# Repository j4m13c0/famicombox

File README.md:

The FamicomBox+ mod has been designed to fix some of the design limitations in the Famicom Box design. The Famicom Box is designed to switch between 16 different cartridges, however in the original design some of the pins in the cartridge are common between the 16 cartridges such as IRQ, M2 and PPU /RD. This mod addresses the following issues:

* Demultiplexes M2 (Pin 38) to all 16 Cartridges
* Multiplexes /IRQ (Pin 15) from all 16 cartridges
* Multiplexes CIRAM /CE (Pin 57) from all 16 cartirdges
* Demultiplexes PPU A12 (pin 64) to all 16 Cartridges
* Demultiplexes PPU /RD (Pin 21) to all 16 Cartridges
* Supplies PPU /A13 (Pin 58) to all cartridges
* Isolates EXP0, EXP1, EXP2, EXP3, EXP4, EXP5, EXP7, EXP8 and EXP9 
* Allows 2 cartridges to utilise EXP6 for Expansion Audio with volume control. 
* Fixes an issue with open bus on games such as Paper Boy
* Disables the second RAM chip 6000 - 7FFF when in game, to allow SRAM and other functions. 
* Enables / Disables $5xxx when in game, this is used in some games and the Everdrive. 

### Famicom Box Warning

On a stock Famicom Box, the EXP Lines are connected to 5V or GND depending on which slot you use. This is used with the CIC to address each CIC individually. Some cartridges use these ports for debugging, Audio etc. If you have a stock Famicom Box you will damage certain cartridge if you plug them in.

### Limitations
This mod is rather complicated to install as there are many parts that you will need to modify to get it to work. You will need to have prior experience with de-soldering IC chips, soldering mod wires and debugging any issues that arise. 
This mod will not work with modern games that have tighter timings, as well as bootleg games bought from places such as AliExpress. 

### Tested Games
I have tested this with the following games:

* Castlevania 3 (Famicom with Expansion Audio)
* The Legend of Zelda
* The Adventure of Link
* Super Mario Bros
* Super Mario Bros 2
* Super Mario Bros 3
* Gauntlet II
* Tetris
* Snake Rattle N Roll
* The Little Mermaid
* Excitebike
* Tennis
* Duck Hunt
* Wrecking Crew
* Captain Planet and the Planeteers
* High Speed
* Yoshi 

I have also been able to use the Famicom Disk System, the RAM adapter will fit in Slot 14. The mod also works with an Everdrive. 

__There may be some games that will not work on this system. This could be down to timing issues. I cannot guarantee any game will work outside of the games tested.__

### Menu System 
The Menu system has been designed by Nintendo to check an internal database of games or for the Nintendo Header in the ROM. Most games do not have a correct header and will not be in the database, thus the game will be rejected. 
 
To get around this, we have modified the menu to still allow games to show up in the menu, however it will only display "NES GAME" instead of the actual game name. 

### 3D Prints
I have included some 3D prints that have used with the Famicom Box.  
 
The Modulator 3D print I used to replace the modulator with some custom connectors with my Famicom Box, I had fitted an NESRGB and this was where I mounted the video and audio connections. This is not required, but added incase you also want to RGB yours. 

The Replacement Coin box covers are the 2 covers on the right-hand side. If you remove the coinbox, you will need these to cover up the holes. 

The 72 Pin connector spacer is helpful if you use the Aliexpress connectors. See the installation guide for more details. 

### Special Thanks

I would like to thank Lidnariq for his time and knowledge to help me make this idea a reality, he was there to teach me what parts were different between the Famicom Box and what parts to include on my mod board. 

I would also like to extend a thank you to Fiskbit, who has helped with reverse engineering the Menu software and modifying it to allow other games to function. He has also improved the menu and fixed some bugs. 
The boot up of the console is now drastically improved due to changes made to the menu.

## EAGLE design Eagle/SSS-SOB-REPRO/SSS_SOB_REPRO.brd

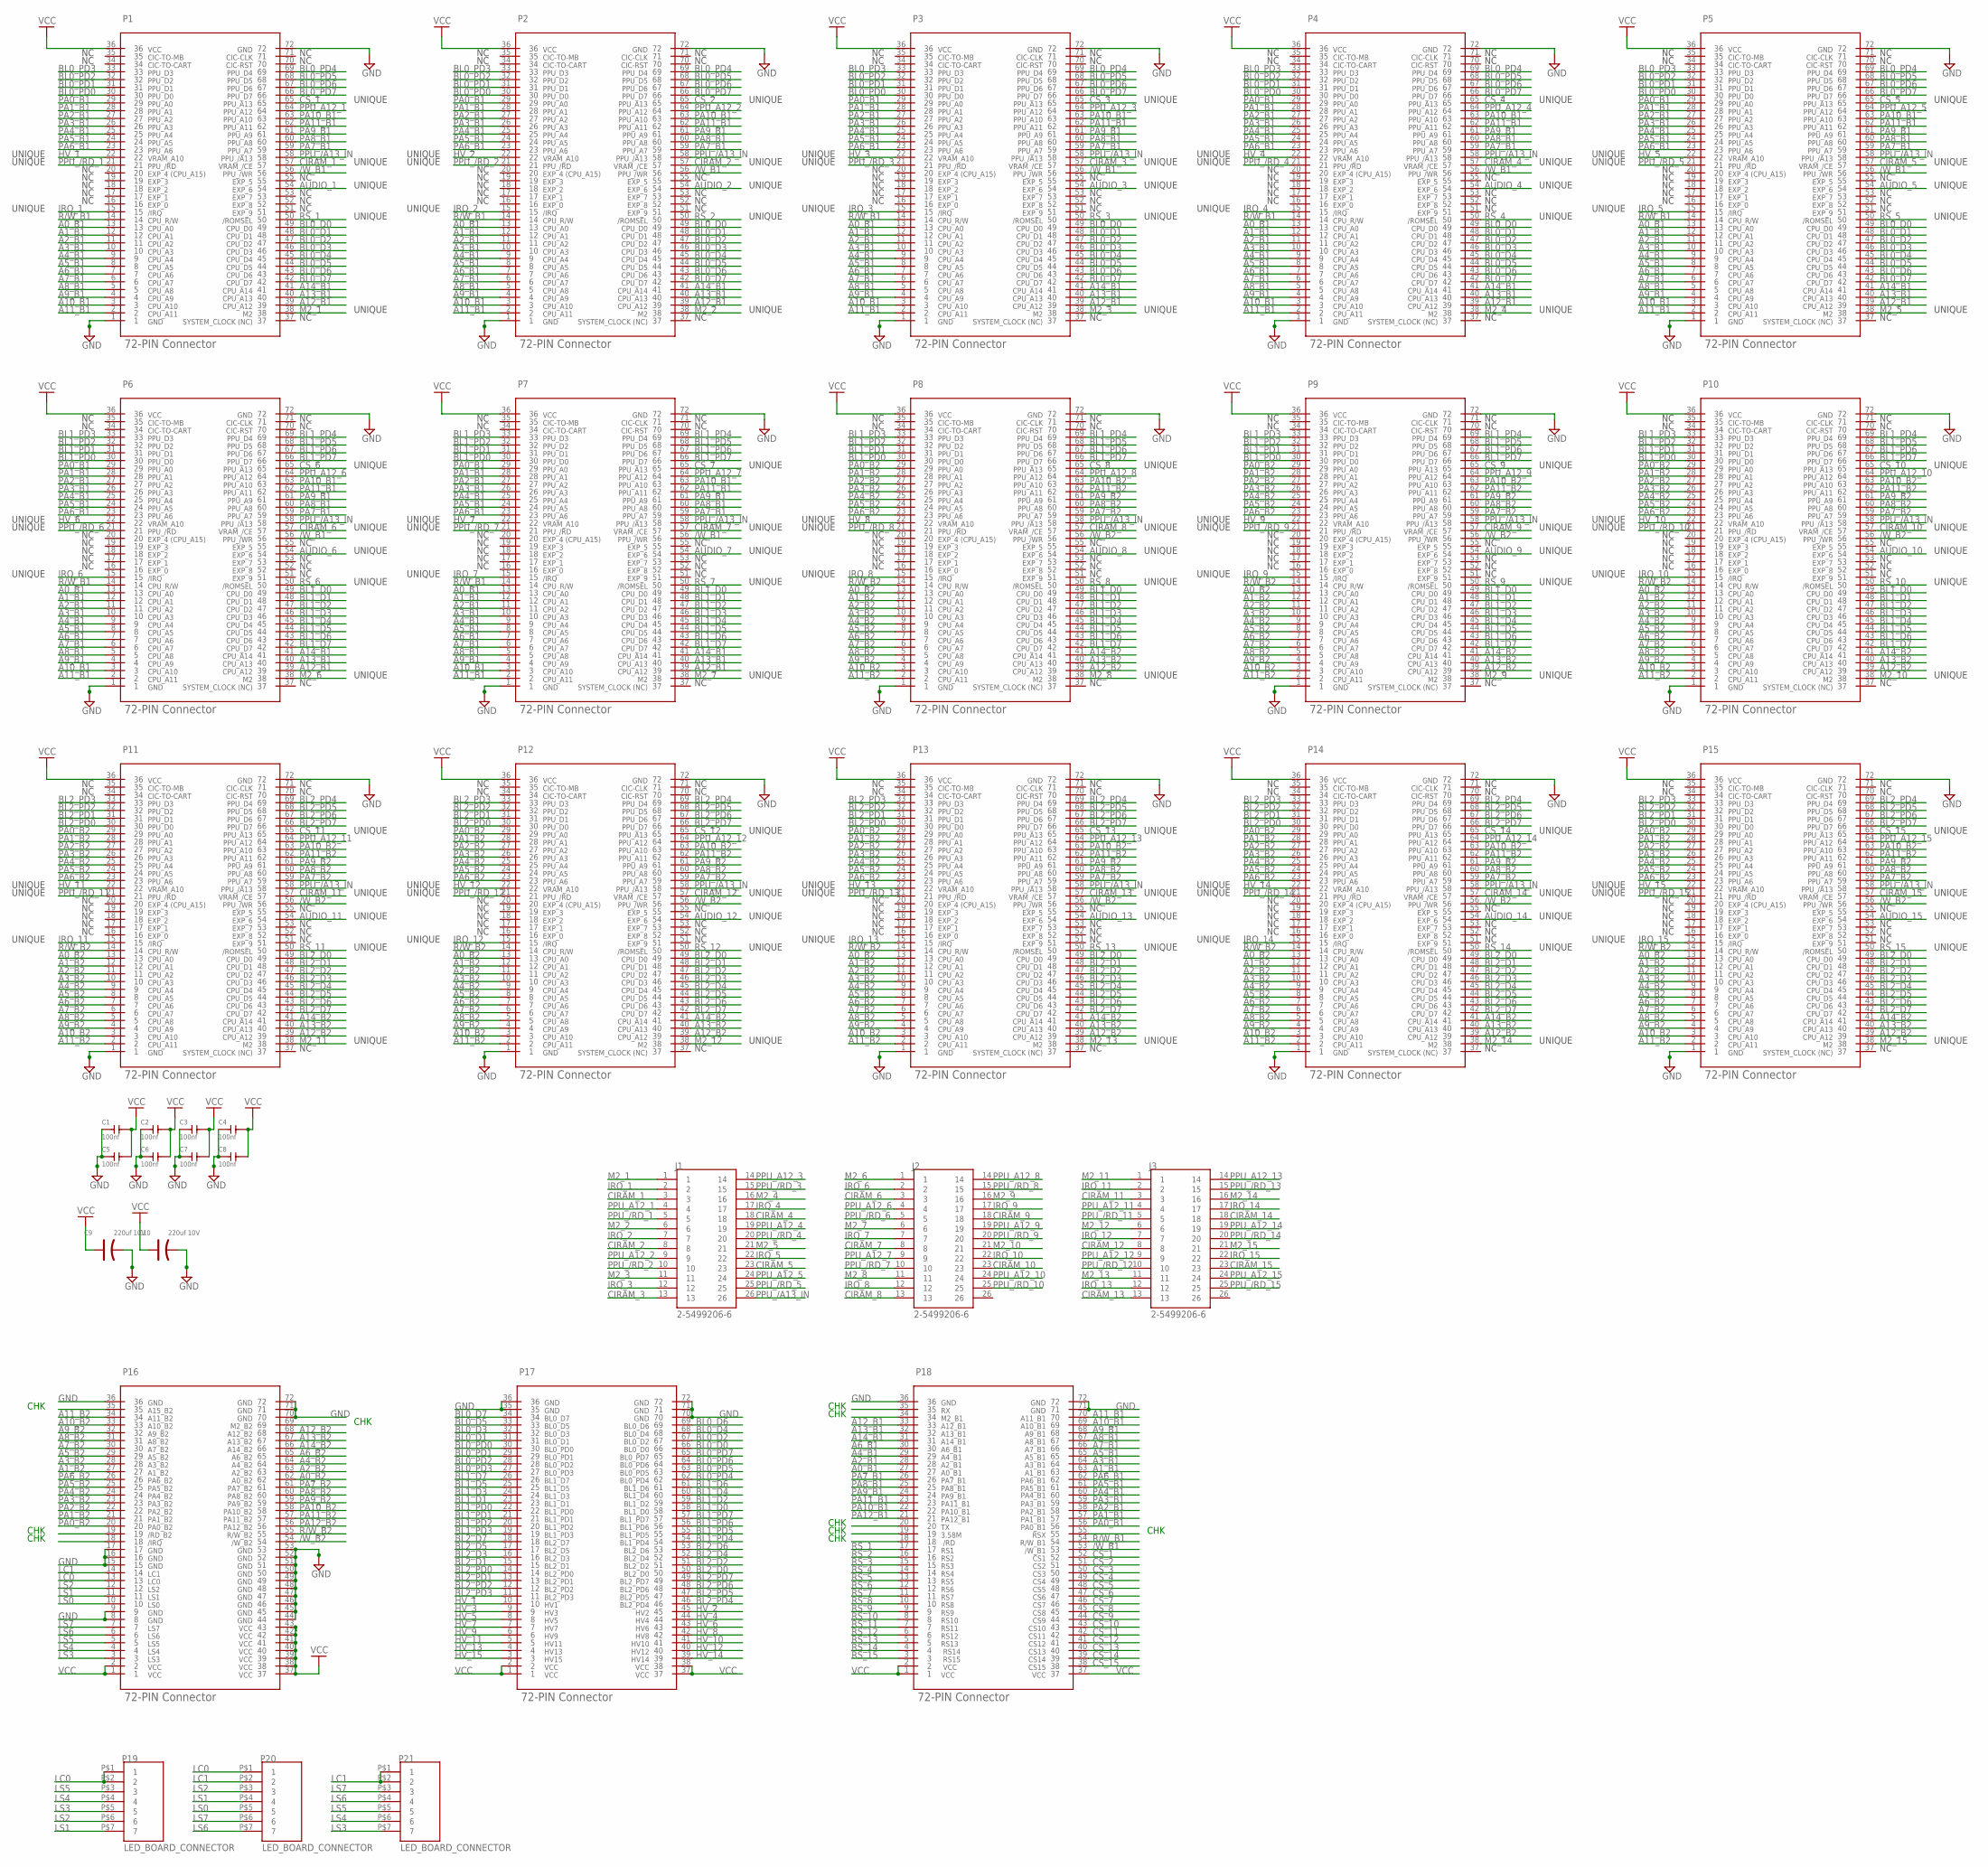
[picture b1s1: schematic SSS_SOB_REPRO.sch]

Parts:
C1, C2, C3, C4, C5, C6, C7, C8: 100nf; C0603
C9, C10: 220uf 10V; PC-D5.3MM
J1, J2, J3: 2-5499206-6; TE_2-5499206-6
P1, P2, P3, P4, P5, P6, P7, P8, P9, P10, P11, P12, P13, P14, P15: CARTRIDGE_CONNECTOR; 72PIN
P16: P16_CONNECTOR; 72PIN
P17: P17_CONNECTOR; 72PIN
P18: P18_CONNECTOR; 72PIN
P19, P20, P21: LED_BOARD_CONNECTOR; 7PIN_LED

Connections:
/RD_B2: P16.19
/W_B1: P1.56, P2.56, P3.56, P4.56, P5.56, P6.56, P7.56, P18.53
/W_B2: P8.56, P9.56, P10.56, P11.56, P12.56, P13.56, P14.56, P15.56, P16.54
A0_B1: P1.13, P2.13, P3.13, P4.13, P5.13, P6.13, P7.13, P18.27
A0_B2: P8.13, P9.13, P10.13, P11.13, P12.13, P13.13, P14.13, P15.13, P16.62
A1_B1: P1.12, P2.12, P3.12, P4.12, P5.12, P6.12, P7.12, P18.63
A1_B2: P8.12, P9.12, P10.12, P11.12, P12.12, P13.12, P14.12, P15.12, P16.27
A2_B1: P1.11, P2.11, P3.11, P4.11, P5.11, P6.11, P7.11, P18.28
A2_B2: P8.11, P9.11, P10.11, P11.11, P12.11, P13.11, P14.11, P15.11, P16.63
A3_B1: P1.10, P2.10, P3.10, P4.10, P5.10, P6.10, P7.10, P18.64
A3_B2: P8.10, P9.10, P10.10, P11.10, P12.10, P13.10, P14.10, P15.10, P16.28
A4_B1: P1.9, P2.9, P3.9, P4.9, P5.9, P6.9, P7.9, P18.29
A4_B2: P8.9, P9.9, P10.9, P11.9, P12.9, P13.9, P14.9, P15.9, P16.64
A5_B1: P1.8, P2.8, P3.8, P4.8, P5.8, P6.8, P7.8, P18.65
A5_B2: P8.8, P9.8, P10.8, P11.8, P12.8, P13.8, P14.8, P15.8, P16.29
A6_B1: P1.7, P2.7, P3.7, P4.7, P5.7, P6.7, P7.7, P18.30
A6_B2: P8.7, P9.7, P10.7, P11.7, P12.7, P13.7, P14.7, P15.7, P16.65
A7_B1: P1.6, P2.6, P3.6, P4.6, P5.6, P6.6, P7.6, P18.66
A7_B2: P8.6, P9.6, P10.6, P11.6, P12.6, P13.6, P14.6, P15.6, P16.30
A8_B1: P1.5, P2.5, P3.5, P4.5, P5.5, P6.5, P7.5, P18.67
A8_B2: P8.5, P9.5, P10.5, P11.5, P12.5, P13.5, P14.5, P15.5, P16.31
A9_B1: P1.4, P2.4, P3.4, P4.4, P5.4, P6.4, P7.4, P18.68
A9_B2: P8.4, P9.4, P10.4, P11.4, P12.4, P13.4, P14.4, P15.4, P16.32
A10_B1: P1.3, P2.3, P3.3, P4.3, P5.3, P6.3, P7.3, P18.69
A10_B2: P8.3, P9.3, P10.3, P11.3, P12.3, P13.3, P14.3, P15.3, P16.33
A11_B1: P1.2, P2.2, P3.2, P4.2, P5.2, P6.2, P7.2, P18.70
A11_B2: P8.2, P9.2, P10.2, P11.2, P12.2, P13.2, P14.2, P15.2, P16.34
A12_B1: P1.39, P2.39, P3.39, P4.39, P5.39, P6.39, P7.39, P18.33
A12_B2: P8.39, P9.39, P10.39, P11.39, P12.39, P13.39, P14.39, P15.39, P16.68
A13_B1: P1.40, P2.40, P3.40, P4.40, P5.40, P6.40, P7.40, P18.32
A13_B2: P8.40, P9.40, P10.40, P11.40, P12.40, P13.40, P14.40, P15.40, P16.67
A14_B1: P1.41, P2.41, P3.41, P4.41, P5.41, P6.41, P7.41, P18.31
A14_B2: P8.41, P9.41, P10.41, P11.41, P12.41, P13.41, P14.41, P15.41, P16.66
A15_B2: P16.35
AUDIO_1: P1.54
AUDIO_2: P2.54
AUDIO_3: P3.54
AUDIO_4: P4.54
AUDIO_5: P5.54
AUDIO_6: P6.54
AUDIO_7: P7.54
AUDIO_8: P8.54
AUDIO_9: P9.54
AUDIO_10: P10.54
AUDIO_11: P11.54
AUDIO_12: P12.54
AUDIO_13: P13.54
AUDIO_14: P14.54
AUDIO_15: P15.54
BL0_D0: P1.49, P2.49, P3.49, P4.49, P5.49, P17.66
BL0_D1: P1.48, P2.48, P3.48, P4.48, P5.48, P17.31
BL0_D2: P1.47, P2.47, P3.47, P4.47, P5.47, P17.67
BL0_D3: P1.46, P2.46, P3.46, P4.46, P5.46, P17.32
BL0_D4: P1.45, P2.45, P3.45, P4.45, P5.45, P17.68
BL0_D5: P1.44, P2.44, P3.44, P4.44, P5.44, P17.33
BL0_D6: P1.43, P2.43, P3.43, P4.43, P5.43, P17.69
BL0_D7: P1.42, P2.42, P3.42, P4.42, P5.42, P17.34
BL0_PD0: P1.30, P2.30, P3.30, P4.30, P5.30, P17.30
BL0_PD1: P1.31, P2.31, P3.31, P4.31, P5.31, P17.29
BL0_PD2: P1.32, P2.32, P3.32, P4.32, P5.32, P17.28
BL0_PD3: P1.33, P2.33, P3.33, P4.33, P5.33, P17.27
BL0_PD4: P1.69, P2.69, P3.69, P4.69, P5.69, P17.62
BL0_PD5: P1.68, P2.68, P3.68, P4.68, P5.68, P17.63
BL0_PD6: P1.67, P2.67, P3.67, P4.67, P5.67, P17.64
BL0_PD7: P1.66, P2.66, P3.66, P4.66, P5.66, P17.65
BL1_D0: P6.49, P7.49, P8.49, P9.49, P10.49, P17.58
BL1_D1: P6.48, P7.48, P8.48, P9.48, P10.48, P17.23
BL1_D2: P6.47, P7.47, P8.47, P9.47, P10.47, P17.59
BL1_D3: P6.46, P7.46, P8.46, P9.46, P10.46, P17.24
BL1_D4: P6.45, P7.45, P8.45, P9.45, P10.45, P17.60
BL1_D5: P6.44, P7.44, P8.44, P9.44, P10.44, P17.25
BL1_D6: P6.43, P7.43, P8.43, P9.43, P10.43, P17.61
BL1_D7: P6.42, P7.42, P8.42, P9.42, P10.42, P17.26
BL1_PD0: P6.30, P7.30, P8.30, P9.30, P10.30, P17.22
BL1_PD1: P6.31, P7.31, P8.31, P9.31, P10.31, P17.21
BL1_PD2: P6.32, P7.32, P8.32, P9.32, P10.32, P17.20
BL1_PD3: P6.33, P7.33, P8.33, P9.33, P10.33, P17.19
BL1_PD4: P6.69, P7.69, P8.69, P9.69, P10.69, P17.54
BL1_PD5: P6.68, P7.68, P8.68, P9.68, P10.68, P17.55
BL1_PD6: P6.67, P7.67, P8.67, P9.67, P10.67, P17.56
BL1_PD7: P6.66, P7.66, P8.66, P9.66, P10.66, P17.57
BL2_D0: P11.49, P12.49, P13.49, P14.49, P15.49, P17.50
BL2_D1: P11.48, P12.48, P13.48, P14.48, P15.48, P17.15
BL2_D2: P11.47, P12.47, P13.47, P14.47, P15.47, P17.51
BL2_D3: P11.46, P12.46, P13.46, P14.46, P15.46, P17.16
BL2_D4: P11.45, P12.45, P13.45, P14.45, P15.45, P17.52
BL2_D5: P11.44, P12.44, P13.44, P14.44, P15.44, P17.17
BL2_D6: P11.43, P12.43, P13.43, P14.43, P15.43, P17.53
BL2_D7: P11.42, P12.42, P13.42, P14.42, P15.42, P17.18
BL2_PD0: P11.30, P12.30, P13.30, P14.30, P15.30, P17.14
BL2_PD1: P11.31, P12.31, P13.31, P14.31, P15.31, P17.13
BL2_PD2: P11.32, P12.32, P13.32, P14.32, P15.32, P17.12
BL2_PD3: P11.33, P12.33, P13.33, P14.33, P15.33, P17.11
BL2_PD4: P11.69, P12.69, P13.69, P14.69, P15.69, P17.46
BL2_PD5: P11.68, P12.68, P13.68, P14.68, P15.68, P17.47
BL2_PD6: P11.67, P12.67, P13.67, P14.67, P15.67, P17.48
BL2_PD7: P11.66, P12.66, P13.66, P14.66, P15.66, P17.49
CIRAM_1: J1.3, P1.57
CIRAM_2: J1.8, P2.57
CIRAM_3: J1.13, P3.57
CIRAM_4: J1.18, P4.57
CIRAM_5: J1.23, P5.57
CIRAM_6: J2.3, P6.57
CIRAM_7: J2.8, P7.57
CIRAM_8: J2.13, P8.57
CIRAM_9: J2.18, P9.57
CIRAM_10: J2.23, P10.57
CIRAM_11: J3.3, P11.57
CIRAM_12: J3.8, P12.57
CIRAM_13: J3.13, P13.57
CIRAM_14: J3.18, P14.57
CIRAM_15: J3.23, P15.57
CS_1: P1.65, P18.52
CS_2: P2.65, P18.51
CS_3: P3.65, P18.50
CS_4: P4.65, P18.49
CS_5: P5.65, P18.48
CS_6: P6.65, P18.47
CS_7: P7.65, P18.46
CS_8: P8.65, P18.45
CS_9: P9.65, P18.44
CS_10: P10.65, P18.43
CS_11: P11.65, P18.42
CS_12: P12.65, P18.41
CS_13: P13.65, P18.40
CS_14: P14.65, P18.39
CS_15: P15.65, P18.38
GND: C1.1, C2.1, C3.1, C4.1, C5.1, C6.1, C7.1, C8.1, C9.-, C10.-, P1.1, P1.72, P2.1, P2.72, P3.1, P3.72, P4.1, P4.72, P5.1, P5.72, P6.1, P6.72, P7.1, P7.72, P8.1, P8.72, P9.1, P9.72, P10.1, P10.72, P11.1, P11.72, P12.1, P12.72, P13.1, P13.72, P14.1, P14.72, P15.1, P15.72, P16.8, P16.9, P16.15, P16.16, P16.17, P16.36, P16.44, P16.45, P16.46, P16.47, P16.48, P16.49, P16.50, P16.51, P16.52, P16.53, P16.70, P16.71, P16.72, P17.35, P17.36, P17.70, P17.71, P17.72, P18.36, P18.71, P18.72
HV_1: P1.22, P17.10
HV_2: P2.22, P17.45
HV_3: P3.22, P17.9
HV_4: P4.22, P17.44
HV_5: P5.22, P17.8
HV_6: P6.22, P17.43
HV_7: P7.22, P17.7
HV_8: P8.22, P17.42
HV_9: P9.22, P17.6
HV_10: P10.22, P17.41
HV_11: P11.22, P17.5
HV_12: P12.22, P17.40
HV_13: P13.22, P17.4
HV_14: P14.22, P17.39
HV_15: P15.22, P17.3
IRQ_1: J1.2, P1.15
IRQ_2: J1.7, P2.15
IRQ_3: J1.12, P3.15
IRQ_4: J1.17, P4.15
IRQ_5: J1.22, P5.15
IRQ_6: J2.2, P6.15
IRQ_7: J2.7, P7.15
IRQ_8: J2.12, P8.15
IRQ_9: J2.17, P9.15
IRQ_10: J2.22, P10.15
IRQ_11: J3.2, P11.15
IRQ_12: J3.7, P12.15
IRQ_13: J3.12, P13.15
IRQ_14: J3.17, P14.15
IRQ_15: J3.22, P15.15
LC0: P16.13, P19.P$1 (1), P19.P$2 (2), P20.P$1 (1)
LC1: P16.14, P20.P$2 (2), P21.P$1 (1), P21.P$2 (2)
LS0: P16.10, P20.P$5 (5)
LS1: P16.11, P19.P$7 (7), P20.P$4 (4)
LS2: P16.12, P19.P$6 (6), P20.P$3 (3)
LS3: P16.3, P19.P$5 (5), P21.P$7 (7)
LS4: P16.4, P19.P$4 (4), P21.P$6 (6)
LS5: P16.5, P19.P$3 (3), P21.P$5 (5)
LS6: P16.6, P20.P$7 (7), P21.P$4 (4)
LS7: P16.7, P20.P$6 (6), P21.P$3 (3)
M2_1: J1.1, P1.38
M2_2: J1.6, P2.38
M2_3: J1.11, P3.38
M2_4: J1.16, P4.38
M2_5: J1.21, P5.38
M2_6: J2.1, P6.38
M2_7: J2.6, P7.38
M2_8: J2.11, P8.38
M2_9: J2.16, P9.38
M2_10: J2.21, P10.38
M2_11: J3.1, P11.38
M2_12: J3.6, P12.38
M2_13: J3.11, P13.38
M2_14: J3.16, P14.38
M2_15: J3.21, P15.38
PA0_B1: P1.29, P2.29, P3.29, P4.29, P5.29, P6.29, P7.29, P18.56
PA0_B2: P8.29, P9.29, P10.29, P11.29, P12.29, P13.29, P14.29, P15.29, P16.20
PA1_B1: P1.28, P2.28, P3.28, P4.28, P5.28, P6.28, P7.28, P18.57
PA1_B2: P8.28, P9.28, P10.28, P11.28, P12.28, P13.28, P14.28, P15.28, P16.21
PA2_B1: P1.27, P2.27, P3.27, P4.27, P5.27, P6.27, P7.27, P18.58
PA2_B2: P8.27, P9.27, P10.27, P11.27, P12.27, P13.27, P14.27, P15.27, P16.22
PA3_B1: P1.26, P2.26, P3.26, P4.26, P5.26, P6.26, P7.26, P18.59
PA3_B2: P8.26, P9.26, P10.26, P11.26, P12.26, P13.26, P14.26, P15.26, P16.23
PA4_B1: P1.25, P2.25, P3.25, P4.25, P5.25, P6.25, P7.25, P18.60
PA4_B2: P8.25, P9.25, P10.25, P11.25, P12.25, P13.25, P14.25, P15.25, P16.24
PA5_B1: P1.24, P2.24, P3.24, P4.24, P5.24, P6.24, P7.24, P18.61
PA5_B2: P8.24, P9.24, P10.24, P11.24, P12.24, P13.24, P14.24, P15.24, P16.25
PA6_B1: P1.23, P2.23, P3.23, P4.23, P5.23, P6.23, P7.23, P18.62
PA6_B2: P8.23, P9.23, P10.23, P11.23, P12.23, P13.23, P14.23, P15.23, P16.26
PA7_B1: P1.59, P2.59, P3.59, P4.59, P5.59, P6.59, P7.59, P18.26
PA7_B2: P8.59, P9.59, P10.59, P11.59, P12.59, P13.59, P14.59, P15.59, P16.61
PA8_B1: P1.60, P2.60, P3.60, P4.60, P5.60, P6.60, P7.60, P18.25
PA8_B2: P8.60, P9.60, P10.60, P11.60, P12.60, P13.60, P14.60, P15.60, P16.60
PA9_B1: P1.61, P2.61, P3.61, P4.61, P5.61, P6.61, P7.61, P18.24
PA9_B2: P8.61, P9.61, P10.61, P11.61, P12.61, P13.61, P14.61, P15.61, P16.59
PA10_B1: P1.63, P2.63, P3.63, P4.63, P5.63, P6.63, P7.63, P18.22
PA10_B2: P8.63, P9.63, P10.63, P11.63, P12.63, P13.63, P14.63, P15.63, P16.58
PA11_B1: P1.62, P2.62, P3.62, P4.62, P5.62, P6.62, P7.62, P18.23
PA11_B2: P8.62, P9.62, P10.62, P11.62, P12.62, P13.62, P14.62, P15.62, P16.57
PA12_B1: P18.21
PA12_B2: P16.56
PPU_/A13_IN: J1.26, P1.58, P2.58, P3.58, P4.58, P5.58, P6.58, P7.58, P8.58, P9.58, P10.58, P11.58, P12.58, P13.58, P14.58, P15.58
PPU_/RD_1: J1.5, P1.21
PPU_/RD_2: J1.10, P2.21
PPU_/RD_3: J1.15, P3.21
PPU_/RD_4: J1.20, P4.21
PPU_/RD_5: J1.25, P5.21
PPU_/RD_6: J2.5, P6.21
PPU_/RD_7: J2.10, P7.21
PPU_/RD_8: J2.15, P8.21
PPU_/RD_9: J2.20, P9.21
PPU_/RD_10: J2.25, P10.21
PPU_/RD_11: J3.5, P11.21
PPU_/RD_12: J3.10, P12.21
PPU_/RD_13: J3.15, P13.21
PPU_/RD_14: J3.20, P14.21
PPU_/RD_15: J3.25, P15.21
PPU_A12_1: J1.4, P1.64
PPU_A12_2: J1.9, P2.64
PPU_A12_3: J1.14, P3.64
PPU_A12_4: J1.19, P4.64
PPU_A12_5: J1.24, P5.64
PPU_A12_6: J2.4, P6.64
PPU_A12_7: J2.9, P7.64
PPU_A12_8: J2.14, P8.64
PPU_A12_9: J2.19, P9.64
PPU_A12_10: J2.24, P10.64
PPU_A12_11: J3.4, P11.64
PPU_A12_12: J3.9, P12.64
PPU_A12_13: J3.14, P13.64
PPU_A12_14: J3.19, P14.64
PPU_A12_15: J3.24, P15.64
R/W_B1: P1.14, P2.14, P3.14, P4.14, P5.14, P6.14, P7.14, P18.54
R/W_B2: P8.14, P9.14, P10.14, P11.14, P12.14, P13.14, P14.14, P15.14, P16.55
RS_1: P1.50, P18.17
RS_2: P2.50, P18.16
RS_3: P3.50, P18.15
RS_4: P4.50, P18.14
RS_5: P5.50, P18.13
RS_6: P6.50, P18.12
RS_7: P7.50, P18.11
RS_8: P8.50, P18.10
RS_9: P9.50, P18.9
RS_10: P10.50, P18.8
RS_11: P11.50, P18.7
RS_12: P12.50, P18.6
RS_13: P13.50, P18.5
RS_14: P14.50, P18.4
RS_15: P15.50, P18.3
VCC: C1.2, C2.2, C3.2, C4.2, C5.2, C6.2, C7.2, C8.2, C9.+, C10.+, P1.36, P2.36, P3.36, P4.36, P5.36, P6.36, P7.36, P8.36, P9.36, P10.36, P11.36, P12.36, P13.36, P14.36, P15.36, P16.1, P16.2, P16.37, P16.38, P16.39, P16.40, P16.41, P16.42, P16.43, P17.1, P17.2, P17.37, P17.38, P18.1, P18.2, P18.37

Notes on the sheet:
UNIQUE
CHK

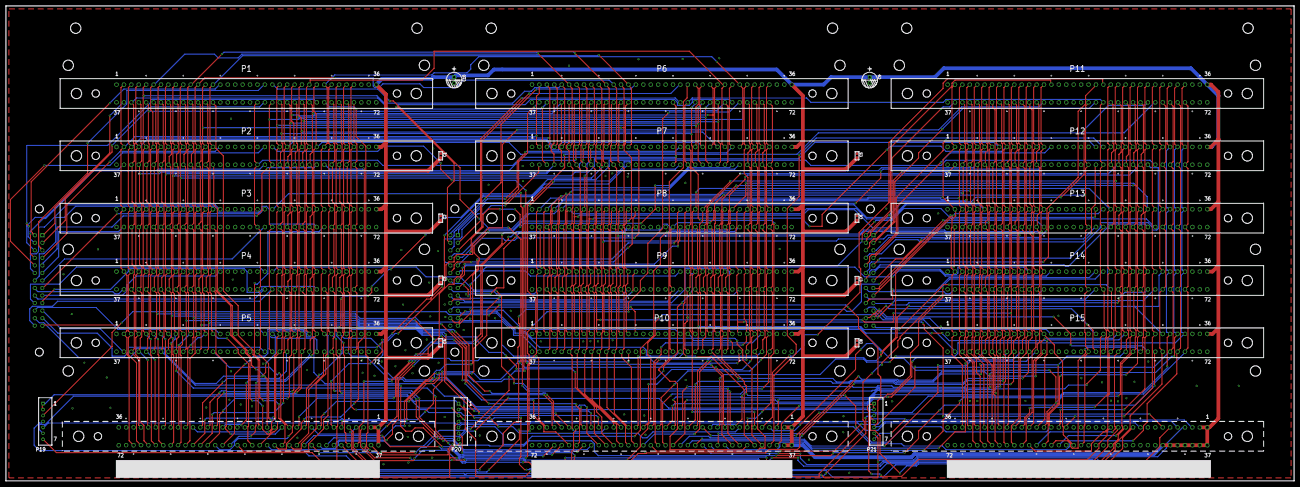
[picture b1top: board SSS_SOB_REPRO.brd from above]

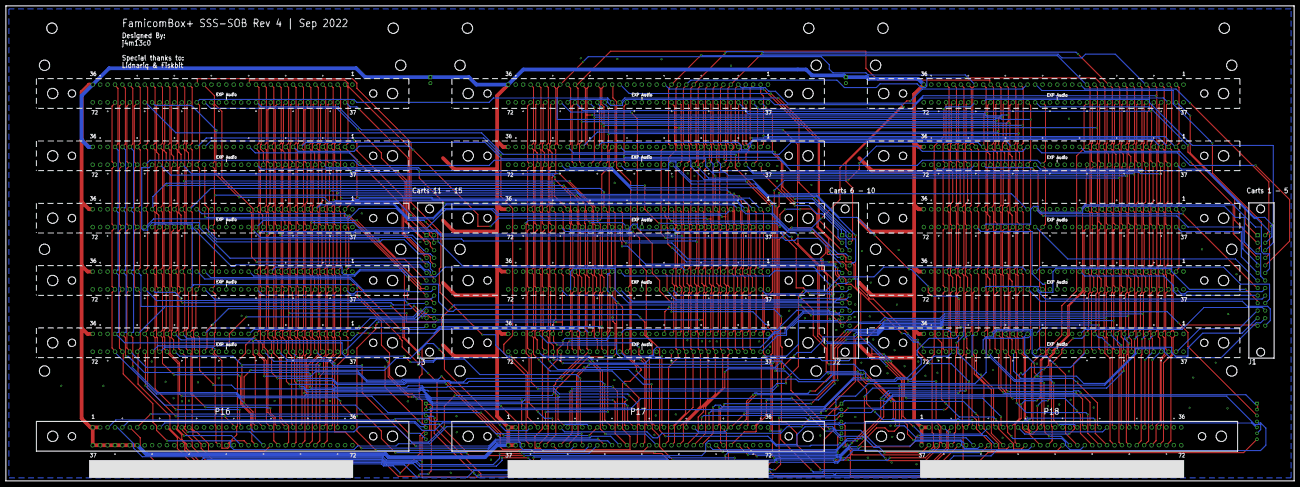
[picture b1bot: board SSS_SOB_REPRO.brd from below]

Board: 2 copper layers, 434.0 x 160.0 mm, 34 parts (6 on the bottom side), 239 nets.

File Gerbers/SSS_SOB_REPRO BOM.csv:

Part,Value,Mouser,
C1,100nf,581-06035C104KAT2A,
C2,100nf,581-06035C104KAT2A,
C3,100nf,581-06035C104KAT2A,
C4,100nf,581-06035C104KAT2A,
C5,100nf,581-06035C104KAT2A,
C6,100nf,581-06035C104KAT2A,
C7,100nf,581-06035C104KAT2A,
C8,100nf,581-06035C104KAT2A,
C9,220uf 10V,647-UFW1A221MED,
C10,220uf 10V,647-UFW1A221MED,
J1,2-5499206-6,571-2-5499206-6,
J1 Cable Conn,1-1658527-0,571-1-1658527-0,
J2,2-5499206-6,571-2-5499206-6,
J2 Cable Conn,1-1658527-0,571-1-1658527-0,
J3,2-5499206-6,571-2-5499206-6,
J3 Cable Conn,1-1658527-0,571-1-1658527-0,
P1,CARTRIDGE_CONNECTOR,https://www.aliexpress.com/item/32785406388.html,
P2,CARTRIDGE_CONNECTOR,https://www.aliexpress.com/item/32785406388.html,
P3,CARTRIDGE_CONNECTOR,https://www.aliexpress.com/item/32785406388.html,
P4,CARTRIDGE_CONNECTOR,https://www.aliexpress.com/item/32785406388.html,
P5,CARTRIDGE_CONNECTOR,https://www.aliexpress.com/item/32785406388.html,
P6,CARTRIDGE_CONNECTOR,https://www.aliexpress.com/item/32785406388.html,
P7,CARTRIDGE_CONNECTOR,https://www.aliexpress.com/item/32785406388.html,
P8,CARTRIDGE_CONNECTOR,https://www.aliexpress.com/item/32785406388.html,
P9,CARTRIDGE_CONNECTOR,https://www.aliexpress.com/item/32785406388.html,
P10,CARTRIDGE_CONNECTOR,https://www.aliexpress.com/item/32785406388.html,
P11,CARTRIDGE_CONNECTOR,https://www.aliexpress.com/item/32785406388.html,
P12,CARTRIDGE_CONNECTOR,https://www.aliexpress.com/item/32785406388.html,
P13,CARTRIDGE_CONNECTOR,https://www.aliexpress.com/item/32785406388.html,
P14,CARTRIDGE_CONNECTOR,https://www.aliexpress.com/item/32785406388.html,
P15,CARTRIDGE_CONNECTOR,https://www.aliexpress.com/item/32785406388.html,
P16,CARTRIDGE_CONNECTOR,https://www.aliexpress.com/item/32785406388.html,
P17,CARTRIDGE_CONNECTOR,https://www.aliexpress.com/item/32785406388.html,
P18,CARTRIDGE_CONNECTOR,https://www.aliexpress.com/item/32785406388.html,
P19,LED_BOARD_CONNECTOR,B7B-PH-K-S(LF)(SN),
P20,LED_BOARD_CONNECTOR,B7B-PH-K-S(LF)(SN),
P21,LED_BOARD_CONNECTOR,B7B-PH-K-S(LF)(SN),

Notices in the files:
parts and their libraries:
m-pad-2.1: License : GNU General Public License version 2 (see bottom)
